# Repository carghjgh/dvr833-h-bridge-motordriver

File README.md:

this is a very small h-bridge using the dvr8833 dual. it it can drive brushed and stepper motors. It is a lot lighter too estamating 2 grams!! I was inspired to making this after i seen how big the l289n is and i wanted to make a much smaller driver controller, so i did it has the same funtonallity too, here is what it looks like-

Schematic-[output.pdf](https://github.com/user-attachments/files/28693864/output.pdf)

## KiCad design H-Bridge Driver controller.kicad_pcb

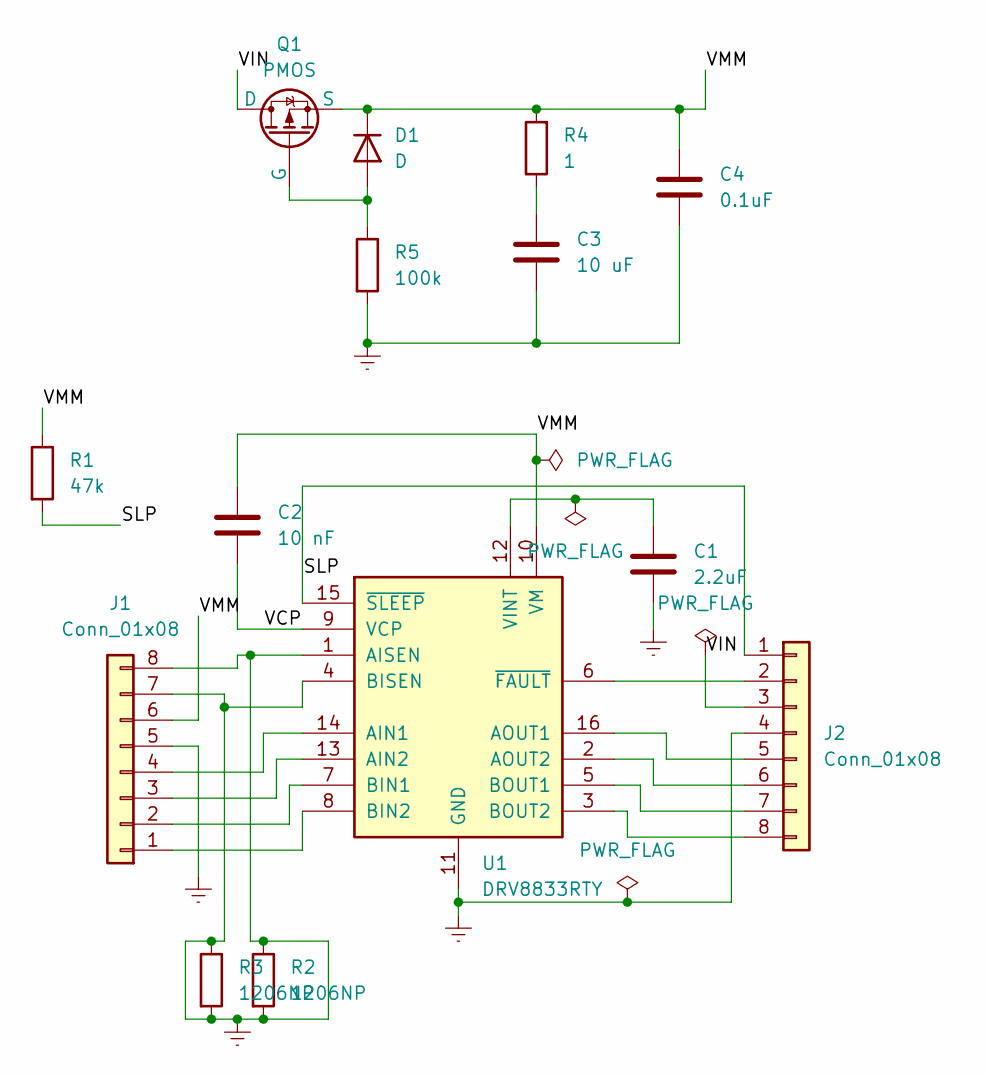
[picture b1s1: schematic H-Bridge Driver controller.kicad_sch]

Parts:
C1: 2.2uF; C_0201_0603Metric_Pad0.64x0.40mm_HandSolder
C2: 10 nF; C_0805_2012Metric_Pad1.18x1.45mm_HandSolder
C3: 10 uF; C_0201_0603Metric_Pad0.64x0.40mm_HandSolder
C4: 0.1uF; C_0201_0603Metric_Pad0.64x0.40mm_HandSolder
D1: D; D_0603_1608Metric_Pad1.05x0.95mm_HandSolder
J1, J2: Conn_01x08; PinHeader_1x08_P1.00mm_Horizontal
Q1: PMOS; SOT-23-3
R1: 47k; R_0805_2012Metric_Pad1.20x1.40mm_HandSolder
R2: 1206NP; R_0612_1632Metric_Pad1.18x3.40mm_HandSolder
R3: 1206NP; R_0603_1608Metric_Pad0.98x0.95mm_HandSolder
R4: 1; R_0201_0603Metric_Pad0.64x0.40mm_HandSolder
R5: 100k; R_0402_1005Metric_Pad0.72x0.64mm_HandSolder
U1: DRV8833RTY; Texas_RTY_WQFN-16-1EP_4x4mm_P0.65mm_EP2.1x2.1mm_ThermalVias

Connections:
/SLP: J2.1, R1.2, U1.15 (~SLEEP)
/VCP: C2.2, U1.9 (VCP)
/VIN: J2.3, Q1.1 (D)
/VMM: C2.1, C4.1, D1.1 (K), J1.6, Q1.3 (S), R1.1, R4.2, U1.10 (VM)
Earth: C1.2, C3.2, C4.2, J1.5, J1.7, J1.8, J2.4, R2.1, R2.2, R3.1, R3.2, R5.2, U1.1 (AISEN), U1.4 (BISEN), U1.11 (GND), U1.17 (GND)
unnamed: C3.1, R4.1
unnamed: D1.2 (A), Q1.2 (G), R5.1
unnamed: J1.1, U1.8 (BIN2)
unnamed: J1.2, U1.7 (BIN1)
unnamed: J1.3, U1.13 (AIN2)
unnamed: J1.4, U1.14 (AIN1)
unnamed: J2.2, U1.6 (~FAULT)
unnamed: J2.5, U1.16 (AOUT1)
unnamed: J2.6, U1.2 (AOUT2)
unnamed: J2.7, U1.5 (BOUT1)
unnamed: J2.8, U1.3 (BOUT2)
unnamed: C1.1, U1.12 (VINT)

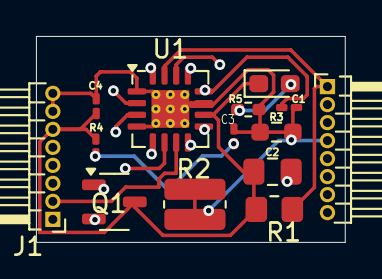
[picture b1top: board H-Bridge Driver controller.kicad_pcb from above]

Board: 4 copper layers, 17.2 x 11.4 mm, 14 parts (0 on the bottom side), 17 nets.

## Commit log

2026-06-08 Add project description for DVR8833 H-bridge
    Added a description of a small H-bridge using the DVR8833 dual driver, including images and a schematic link.
2026-06-08 Fix typos and enhance README content
    Correct typos and improve clarity in project description.
2026-06-08 Update README.md for clarity and corrections
    Corrected typos and improved clarity in the project description.
